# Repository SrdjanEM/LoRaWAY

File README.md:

# LoRaWAY

LoRaWAY is an ESP32-C3–based project that interfaces with the **KG200Z LoRa module** to enable both **peer-to-peer (P2P) LoRa communication** and **LoRaWAN connectivity**.

The ESP32-C3 acts as a controller and bridge, handling configuration, command parsing, and data exchange with the KG200Z module via AT commands.

## Features

* 📡 **LoRa P2P communication**

  * Direct device-to-device data exchange
  * Suitable for testing, prototyping, and local networks
* 🌍 **LoRaWAN support**

  * Ability to join and communicate with a LoRaWAN network
  * Supports standard LoRaWAN workflows (join, uplink, downlink)
* 🔁 **Flexible data handling**

  * Exchange various types of information (sensor data, status, commands)
* ⚙️ **ESP32-C3 control**

  * Configuration and communication managed by ESP32-C3 firmware
  * Easy integration with additional peripherals if needed

## Hardware

* **MCU:** ESP32-C3
* **LoRa Module:** KG200Z
* **Communication Interface:** UART (AT commands)

## Project Structure

* ESP32-C3 firmware handles:

  * KG200Z initialization
  * Mode switching (P2P ↔ LoRaWAN)
  * Data transmission and reception
* KG200Z module handles:

  * LoRa radio operations
  * Network communication

Features and functionality may be expanded as development continues.

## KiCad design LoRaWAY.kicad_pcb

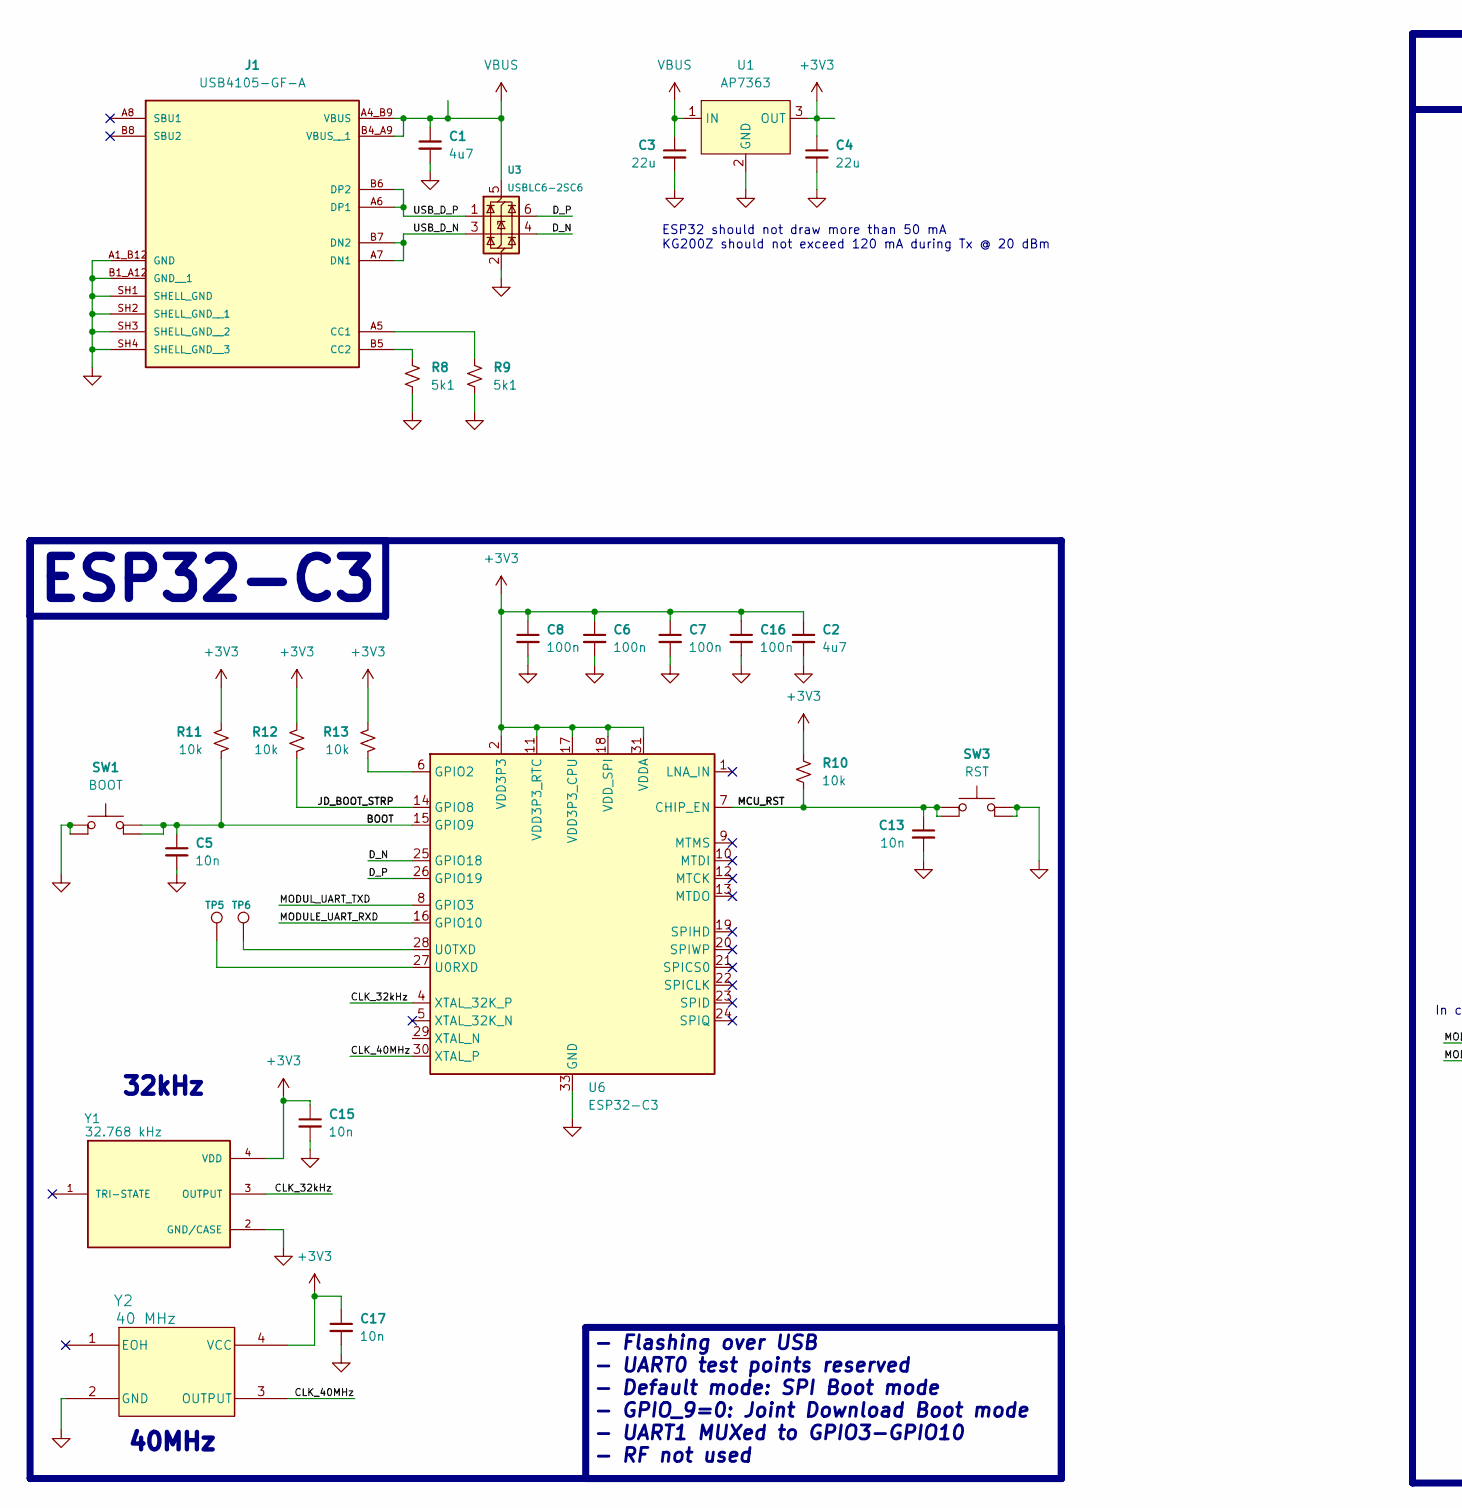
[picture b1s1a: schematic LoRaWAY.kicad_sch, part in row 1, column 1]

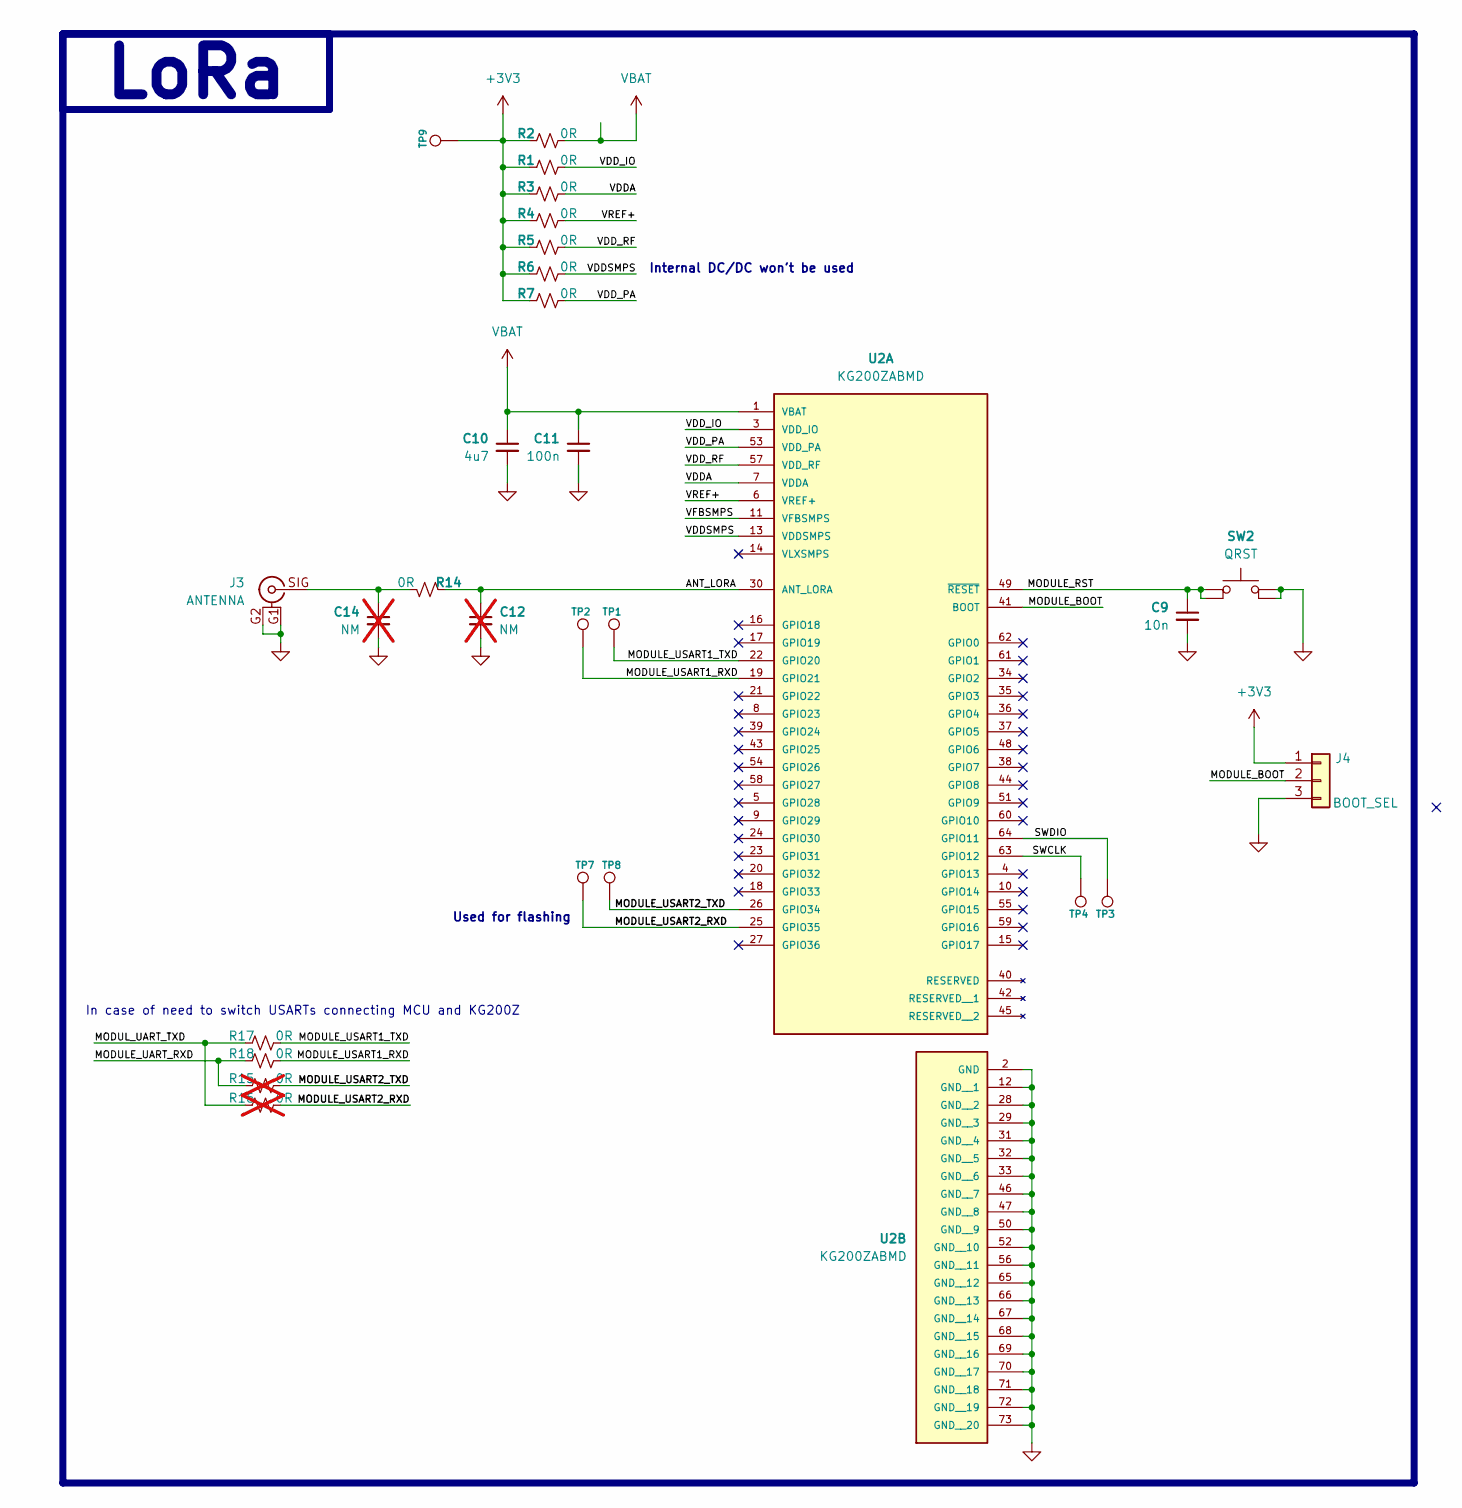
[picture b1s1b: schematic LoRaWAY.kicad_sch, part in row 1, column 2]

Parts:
C1, C2, C10: 4u7; C_0402_1005Metric
C3, C4: 22u; C_0402_1005Metric
C5, C9, C13, C15, C17: 10n; C_0402_1005Metric
C6, C7, C8, C11, C16: 100n; C_0402_1005Metric
C12, C14: NM; C_0402_1005Metric; not fitted
J1: USB4105-GF-A; GCT_USB4105-GF-A
J3: ANTENNA; HIROSE_U.FL-R-SMT-1_80_
J4: BOOT_SEL; PinHeader_1x03_P2.54mm_Vertical
R1, R2, R3, R4, R5, R6, R7, R14, R17, R18: 0R; R_0402_1005Metric
R8, R9: 5k1; R_0402_1005Metric
R10, R11, R12, R13: 10k; R_0402_1005Metric
R15, R16: 0R; R_0402_1005Metric; not fitted
SW1: BOOT; SW4_PTS815 SJM 250 SMTR LFS_CNK
SW2: QRST; SW4_PTS815 SJM 250 SMTR LFS_CNK
SW3: RST; SW4_PTS815 SJM 250 SMTR LFS_CNK
TP1, TP2, TP3, TP4, TP5, TP6, TP7, TP8, TP9: TestPoint; TestPoint_Pad_D1.0mm
U1: AP7363; TO252-3L_DIO; MPN AP7363-33D-13
U2: KG200ZABMD; XCVR_KG200ZABMD; PARTREV 1.0
U3: USBLC6-2SC6; SOT-23-6
U6: ESP32-C3; QFN-32-1EP_5x5mm_P0.5mm_EP3.7x3.7mm
Y1: 32.768 kHz; XTAL_ASEK-32.768KHZ-L-R-T; MPN ASEK-32.768KHZ-L-R-T
Y2: 40 MHz; IC_625L3C040M00000_CTS; MPN 625L3C040M00000

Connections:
+3V3: C2.1, C4.1, C6.1, C7.1, C8.1, C15.1, C16.1, C17.1, J4.1, R1.1, R2.1, R3.1, R4.1, R5.1, R6.1, R7.1, R10.1, R11.1, R12.1, R13.1, TP9.1, U1.3 (OUT), U6.2 (VDD3P3), U6.3 (VDD3P3), U6.11 (VDD3P3_RTC), U6.17 (VDD3P3_CPU), U6.18 (VDD_SPI), U6.31 (VDDA), U6.32 (VDDA), Y1.4 (VDD), Y2.4 (VCC)
/ANT_LORA: C12.1, R14.1, U2.30 (ANT_LORA)
/BOOT: C5.1, R11.2, SW1.1, SW1.2, U6.15 (GPIO9)
/CLK_32kHz: U6.4 (XTAL_32K_P), Y1.3 (OUTPUT)
/CLK_40MHz: U6.30 (XTAL_P), Y2.3 (OUTPUT)
/D_N: U3.4 (I/O2), U6.25 (GPIO18)
/D_P: U3.6 (I/O1), U6.26 (GPIO19)
/JD_BOOT_STRP: R12.2, U6.14 (GPIO8)
/MCU_RST: C13.1, R10.2, SW3.3, SW3.4 (3), U6.7 (CHIP_EN)
/MODULE_BOOT: J4.2, U2.41 (BOOT)
/MODULE_RST: C9.1, SW2.3, SW2.4 (3), U2.49 (~RESET)
/MODULE_UART_RXD: R15.1, R18.1, U6.16 (GPIO10)
/MODULE_USART1_RXD: R18.2, TP2.1, U2.19 (GPIO21)
/MODULE_USART1_TXD: R17.2, TP1.1, U2.22 (GPIO20)
/MODULE_USART2_RXD: R16.2, TP7.1, U2.25 (GPIO35)
/MODULE_USART2_TXD: R15.2, TP8.1, U2.26 (GPIO34)
/MODUL_UART_TXD: R16.1, R17.1, U6.8 (GPIO3)
/SWCLK: TP4.1, U2.63 (GPIO12)
/SWDIO: TP3.1, U2.64 (GPIO11)
/USB_D_N: J1.A7 (DN1), J1.B7 (DN2), U3.3 (I/O2)
/USB_D_P: J1.A6 (DP1), J1.B6 (DP2), U3.1 (I/O1)
/VDDA: R3.2, U2.7 (VDDA)
/VDDSMPS: R6.2, U2.13 (VDDSMPS)
/VDD_IO: R1.2, U2.3 (VDD_IO)
/VDD_PA: R7.2, U2.53 (VDD_PA)
/VDD_RF: R5.2, U2.57 (VDD_RF)
/VFBSMPS: U2.11 (VFBSMPS)
/VREF+: R4.2, U2.6 (VREF+)
GND: C1.2, C2.2, C3.2, C4.2, C5.2, C6.2, C7.2, C8.2, C9.2, C10.2, C11.2, C12.2, C13.2, C14.2, C15.2, C16.2, C17.2, J1.A1_B12 (GND), J1.B1_A12 (GND__1), J1.SH1 (SHELL_GND), J1.SH2 (SHELL_GND__1), J1.SH3 (SHELL_GND__2), J1.SH4 (SHELL_GND__3), J3.G1 (Ext), J3.G2 (Ext), J4.3, R8.2, R9.2, SW1.3, SW1.4 (3), SW2.1, SW2.2, SW3.1, SW3.2, U1.2 (GND), U2.2 (GND), U2.12 (GND__1), U2.28 (GND__2), U2.29 (GND__3), U2.31 (GND__4), U2.32 (GND__5), U2.33 (GND__6), U2.46 (GND__7), U2.47 (GND__8), U2.50 (GND__9), U2.52 (GND__10), U2.56 (GND__11), U2.65 (GND__12), U2.66 (GND__13), U2.67 (GND__14), U2.68 (GND__15), U2.69 (GND__16), U2.70 (GND__17), U2.71 (GND__18), U2.72 (GND__19), U2.73 (GND__20), U3.2 (GND), U6.33 (GND), Y1.2 (GND/CASE), Y2.2 (GND)
unnamed: J1.A5 (CC1), R9.1
unnamed: J1.B5 (CC2), R8.1
unnamed: C14.1, J3.SIG (In), R14.2
unnamed: R13.2, U6.6 (GPIO2)
unnamed: TP5.1, U6.27 (U0RXD)
unnamed: TP6.1, U6.28 (U0TXD)
VBAT: C10.1, C11.1, R2.2, U2.1 (VBAT)
VBUS: C1.1, C3.1, J1.A4_B9 (VBUS), J1.B4_A9 (VBUS__1), U1.1 (IN), U3.5 (VBUS)

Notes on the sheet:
Internal DC/DC won't be used
ESP32 should not draw more than 50 mA KG200Z should not exceed 120 mA during Tx @ 20 dBm
In case of need to switch USARTs connecting MCU and KG200Z
40MHz
32kHz
Used for flashing
LoRa
- Flashing over USB - UART0 test points reserved - Default mode: SPI Boot mode - GPIO_9=0: Joint Download Boot mode - UART1 MUXed to GPIO3-GPIO10 - RF not used
ESP32-C3

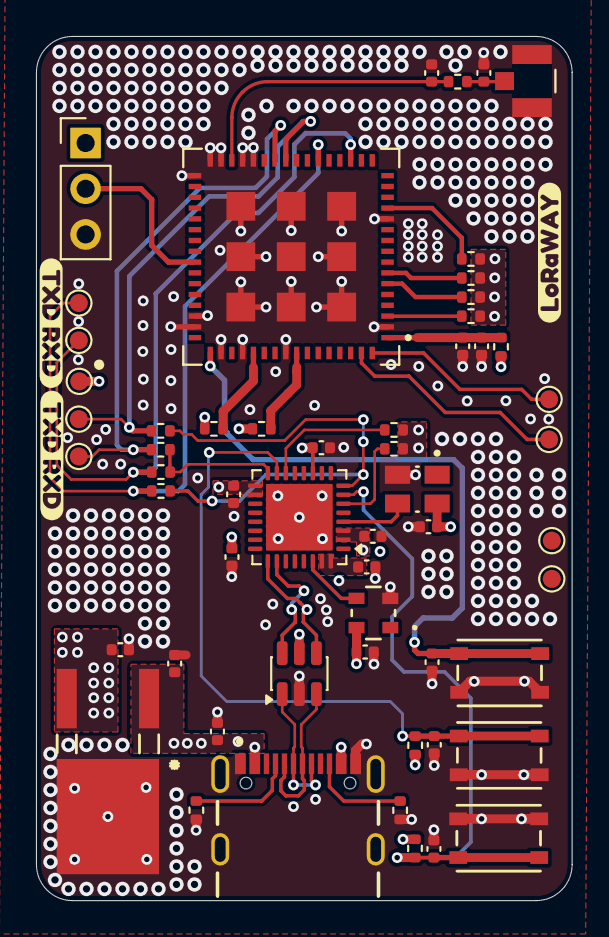
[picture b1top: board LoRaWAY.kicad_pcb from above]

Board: 4 copper layers, 29.8 x 48.0 mm, 59 parts (0 on the bottom side), 36 nets.

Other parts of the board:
kibuzzard-69502FA5: G***; kibuzzard-69502FA5
kibuzzard-694845CE, kibuzzard-694845CE#2: G***; kibuzzard-694845CE

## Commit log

2025-12-21 Review request
2025-12-28 Pre-release v1.0
2025-12-28 Initialize README with project details
    Added project overview, features, hardware specifications, and structure.
2025-12-28 3D render
2025-12-28 Add image to README for LoRaWAY project
    Added an image to the README for visual representation.
2025-12-28 Update LoRa badge to Quectel KG200Z
2026-02-09 Final design
